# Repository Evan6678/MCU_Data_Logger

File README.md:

# MCU Data Logger

The MCU Data Logger is a compact ATmega328P-based board designed with integrated real-time clock and EEPROM storage, providing a foundation for timestamped data collection from external sensors and peripherals. This project demonstrates two PCB design revisions, showcasing both a traditional two-layer layout and a more advanced four-layer compact layout. The goal of this board is to practice designing microcontroller-based hardware, integrating I2C peripherals, and producing increasingly complex PCB layouts as part of a broader progression toward custom embedded hardware development.

---

## Schematic

The circuit integrates three primary components: the ATmega328P-AU microcontroller, a DS1337S real-time clock with 32.768 kHz crystal, and two 24LC1025 EEPROMs for non-volatile storage. Each device communicates over I2C, with breakout headers provided for GPIO, UART programming, ICSP, and battery or 5 V power input.

**Schematic PDF:** [Schematic PDF](ReadmeResources/PcbSchematicMainPage.pdf)

---

## Two-Layer PCB Revision

This version uses a two-layer board with components placed on a single side, following a more traditional layout approach. It offers clear routing, easier hand assembly, and a straightforward component arrangement appropriate for early prototyping.

### 3D Model Views

#### Front View

#### Angled View

### PCB Layout

**2-Layer PCB Layout PDF:** [Layout Document](`ReadmeResources/2LayerPcbLayout.pdf`)

---

## Four-Layer PCB Revision

The four-layer revision introduces a more compact footprint with components on both sides and a denser routing strategy. This version leverages additional layers for power, ground, and signal separation, providing an opportunity to practice modern multi-layer design techniques.

### 3D Model Views

#### Front View

#### Back View

#### Angled View

### PCB Layout

**4-Layer PCB Layout PDF:** [Layout Document](`ReadmeResources/4LayerPcbLayout.pdf`)

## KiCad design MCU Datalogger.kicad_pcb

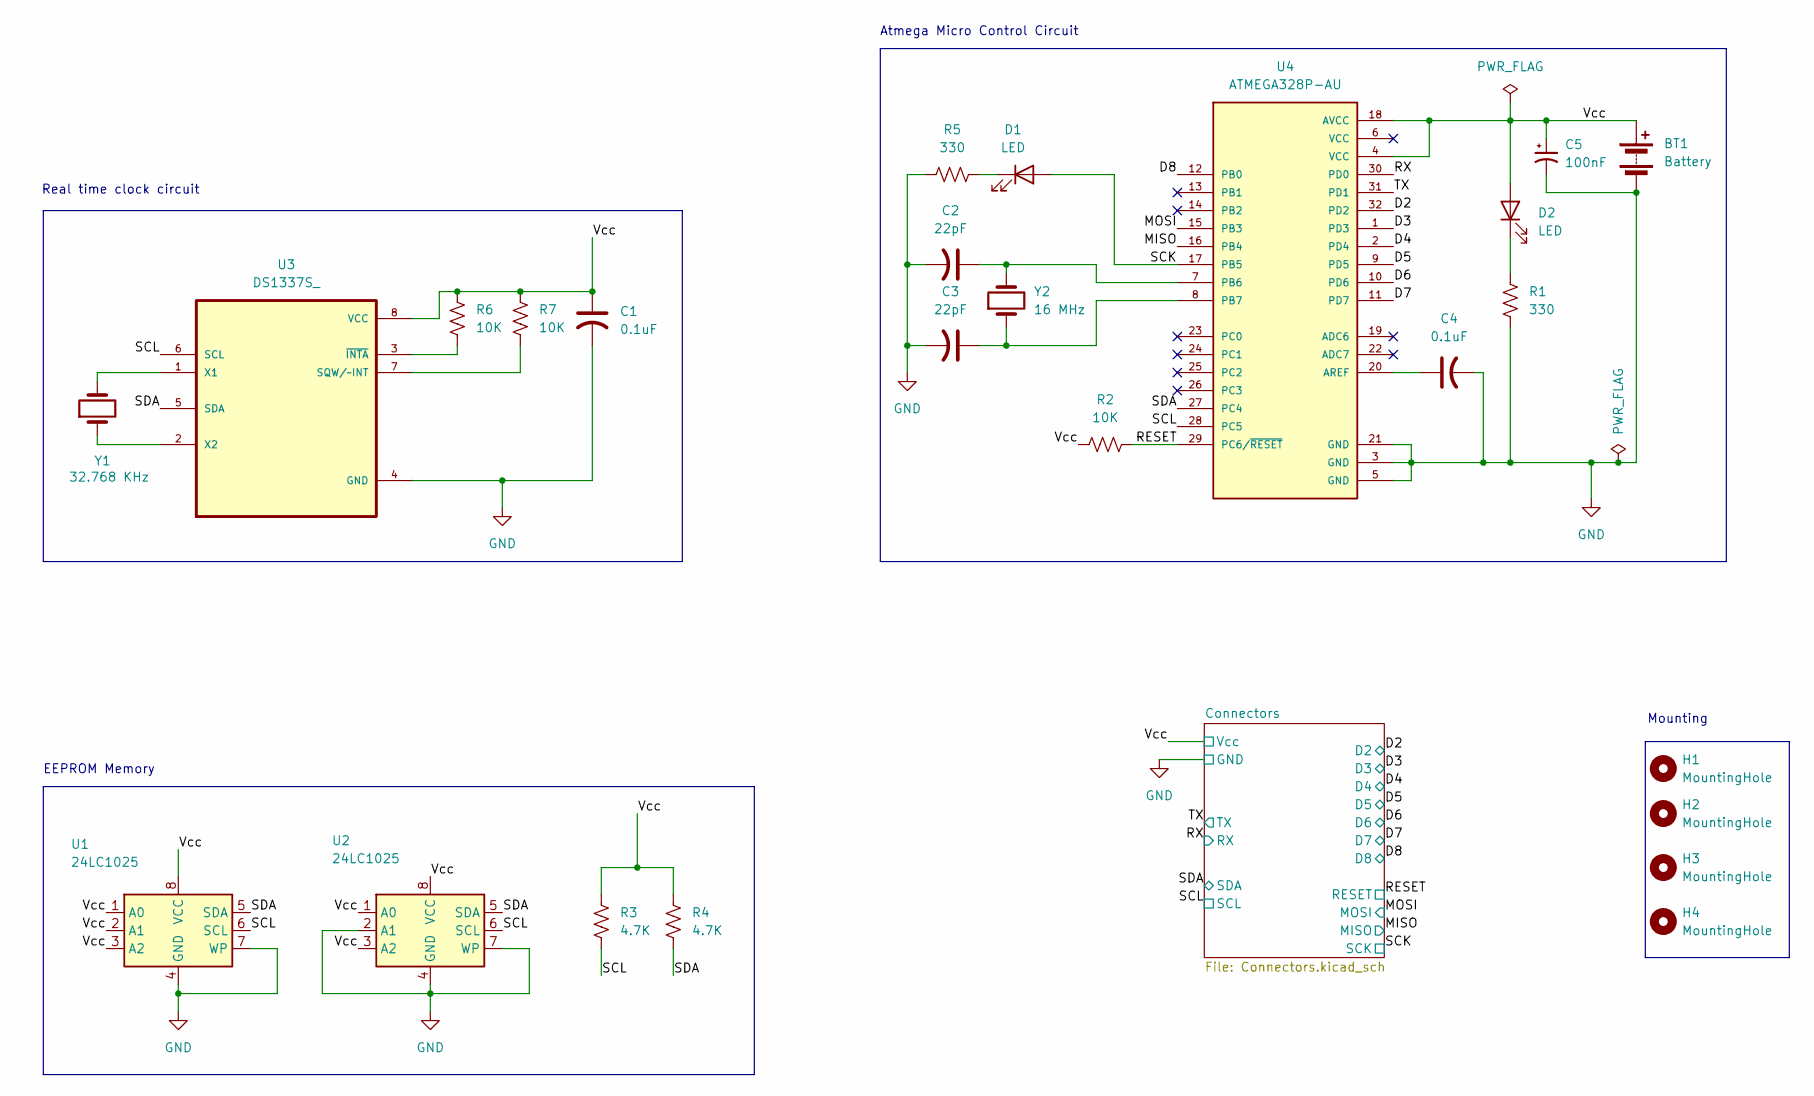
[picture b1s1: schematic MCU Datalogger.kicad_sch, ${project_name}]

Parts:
BT1: Battery; PinHeader_1x02_P2.54mm_Vertical
C1, C4: 0.1uF; C_0805_2012Metric
C2, C3: 22pF; C_0805_2012Metric
C5: 100nF; C_0805_2012Metric
D1, D2: LED; LED_0805_2012Metric
H1, H2, H3, H4: MountingHole; MountingHole_2.1mm
R1, R5: 330; R_0805_2012Metric
R2, R6, R7: 10K; R_0805_2012Metric
R3, R4: 4.7K; R_0805_2012Metric
U1, U2: 24LC1025; SOIC-8_5.3x5.3mm_P1.27mm
U3: DS1337S_; SOIC127P600X175-8N
U4: ATMEGA328P-AU; QFP80P900X900X120-32N; PARTREV 8271A
Y1: 32.768 KHz; Crystal_SMD_5032-2Pin_5.0x3.2mm_HandSoldering
Y2: 16 MHz; Crystal_SMD_5032-2Pin_5.0x3.2mm_HandSoldering

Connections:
/D2: U4.32 (PD2); also elsewhere on the board
/D3: U4.1 (PD3); also elsewhere on the board
/D4: U4.2 (PD4); also elsewhere on the board
/D5: U4.9 (PD5); also elsewhere on the board
/D6: U4.10 (PD6); also elsewhere on the board
/D7: U4.11 (PD7); also elsewhere on the board
/D8: U4.12 (PB0); also elsewhere on the board
/MISO: U4.16 (PB4); also elsewhere on the board
/MOSI: U4.15 (PB3); also elsewhere on the board
/RESET: R2.2, U4.29 (PC6/~RESET); also elsewhere on the board
/RX: U4.30 (PD0); also elsewhere on the board
/SCK: D1.2 (A), U4.17 (PB5); also elsewhere on the board
/SCL: R3.2, U1.6 (SCL), U2.6 (SCL), U3.6 (SCL), U4.28 (PC5); also elsewhere on the board
/SDA: R4.2, U1.5 (SDA), U2.5 (SDA), U3.5 (SDA), U4.27 (PC4); also elsewhere on the board
/TX: U4.31 (PD1); also elsewhere on the board
/Vcc: BT1.1 (+), C1.1, C5.1, D2.2 (A), R2.1, R3.1, R4.1, R6.1, R7.1, U1.1 (A0), U1.2 (A1), U1.3 (A2), U1.8 (VCC), U2.1 (A0), U2.3 (A2), U2.8 (VCC), U3.8 (VCC), U4.4 (VCC), U4.18 (AVCC); also elsewhere on the board
GND: BT1.2 (-), C1.2, C2.2, C3.2, C4.2, C5.2, R1.2, R5.1, U1.4 (GND), U1.7 (WP), U2.2 (A1), U2.4 (GND), U2.7 (WP), U3.4 (GND), U4.3 (GND), U4.5 (GND), U4.21 (GND); also elsewhere on the board
unnamed: D1.1 (K), R5.2
unnamed: D2.1 (K), R1.1
unnamed: R7.2, U3.7 (SQW/~INT)
unnamed: U3.1 (X1), Y1.2
unnamed: U3.2 (X2), Y1.1
unnamed: R6.2, U3.3 (~INTA)
unnamed: C4.1, U4.20 (AREF)
unnamed: C2.1, U4.7 (PB6), Y2.2
unnamed: C3.1, U4.8 (PB7), Y2.1

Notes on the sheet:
Real time clock circuit
Atmega Micro Control Circuit
EEPROM Memory
Mounting

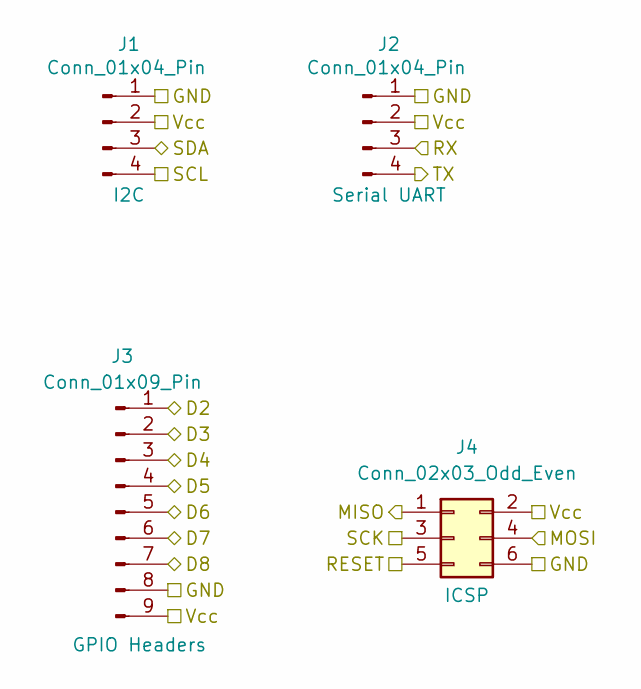
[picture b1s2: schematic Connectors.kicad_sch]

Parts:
J1, J2: Conn_01x04_Pin; PinHeader_1x04_P2.54mm_Vertical
J3: Conn_01x09_Pin; PinHeader_1x09_P2.54mm_Vertical
J4: Conn_02x03_Odd_Even; PinHeader_2x03_P2.54mm_Vertical

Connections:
/D2: J3.1; also elsewhere on the board
/D3: J3.2; also elsewhere on the board
/D4: J3.3; also elsewhere on the board
/D5: J3.4; also elsewhere on the board
/D6: J3.5; also elsewhere on the board
/D7: J3.6; also elsewhere on the board
/D8: J3.7; also elsewhere on the board
/MISO: J4.1; also elsewhere on the board
/MOSI: J4.4; also elsewhere on the board
/RESET: J4.5; also elsewhere on the board
/RX: J2.3; also elsewhere on the board
/SCK: J4.3; also elsewhere on the board
/SCL: J1.4; also elsewhere on the board
/SDA: J1.3; also elsewhere on the board
/TX: J2.4; also elsewhere on the board
/Vcc: J1.2, J2.2, J3.9, J4.2; also elsewhere on the board
GND: J1.1, J2.1, J3.8, J4.6; also elsewhere on the board

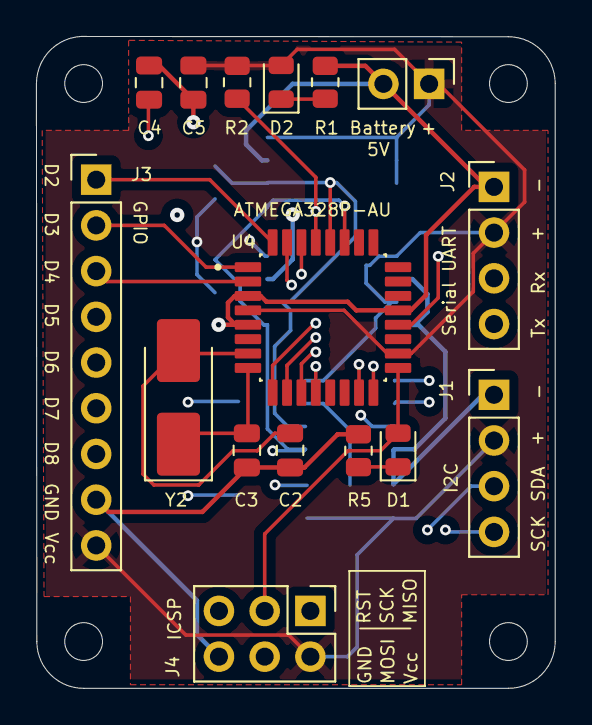
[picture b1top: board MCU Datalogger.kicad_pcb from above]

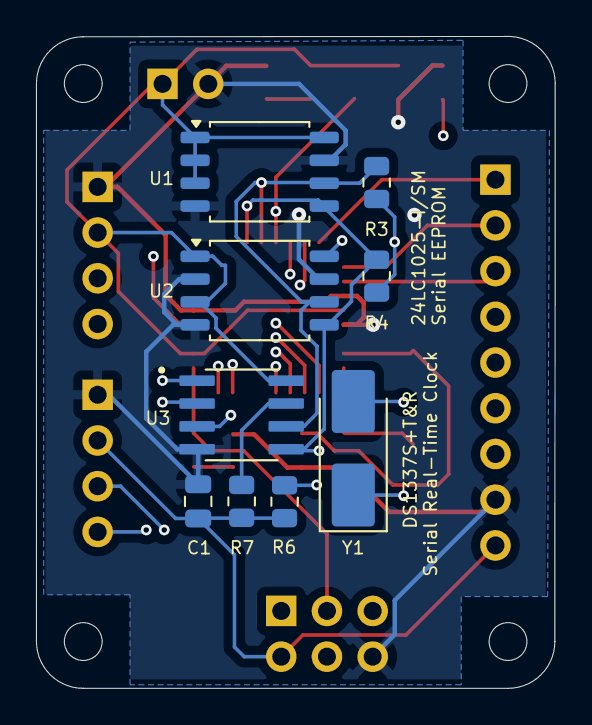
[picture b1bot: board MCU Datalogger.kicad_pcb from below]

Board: 4 copper layers, 28.8 x 36.2 mm, 29 parts (9 on the bottom side), 26 nets.

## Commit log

2025-11-19 init project
2025-11-20 project Setup
2025-11-28 finish schematic process for MCU data logger
2025-11-29 update gitignore file
2025-11-30 first revision tracks
2025-12-01 Re-design 2 layer board
2025-12-01 save changes
2025-12-01 fix DRC error
2025-12-01 started 2 sided board
2025-12-01 Fix Clock Bug
2025-12-01 fixed routing bug
2025-12-01 route PCB
2025-12-01 saved changes
2025-12-01 Add Readme
